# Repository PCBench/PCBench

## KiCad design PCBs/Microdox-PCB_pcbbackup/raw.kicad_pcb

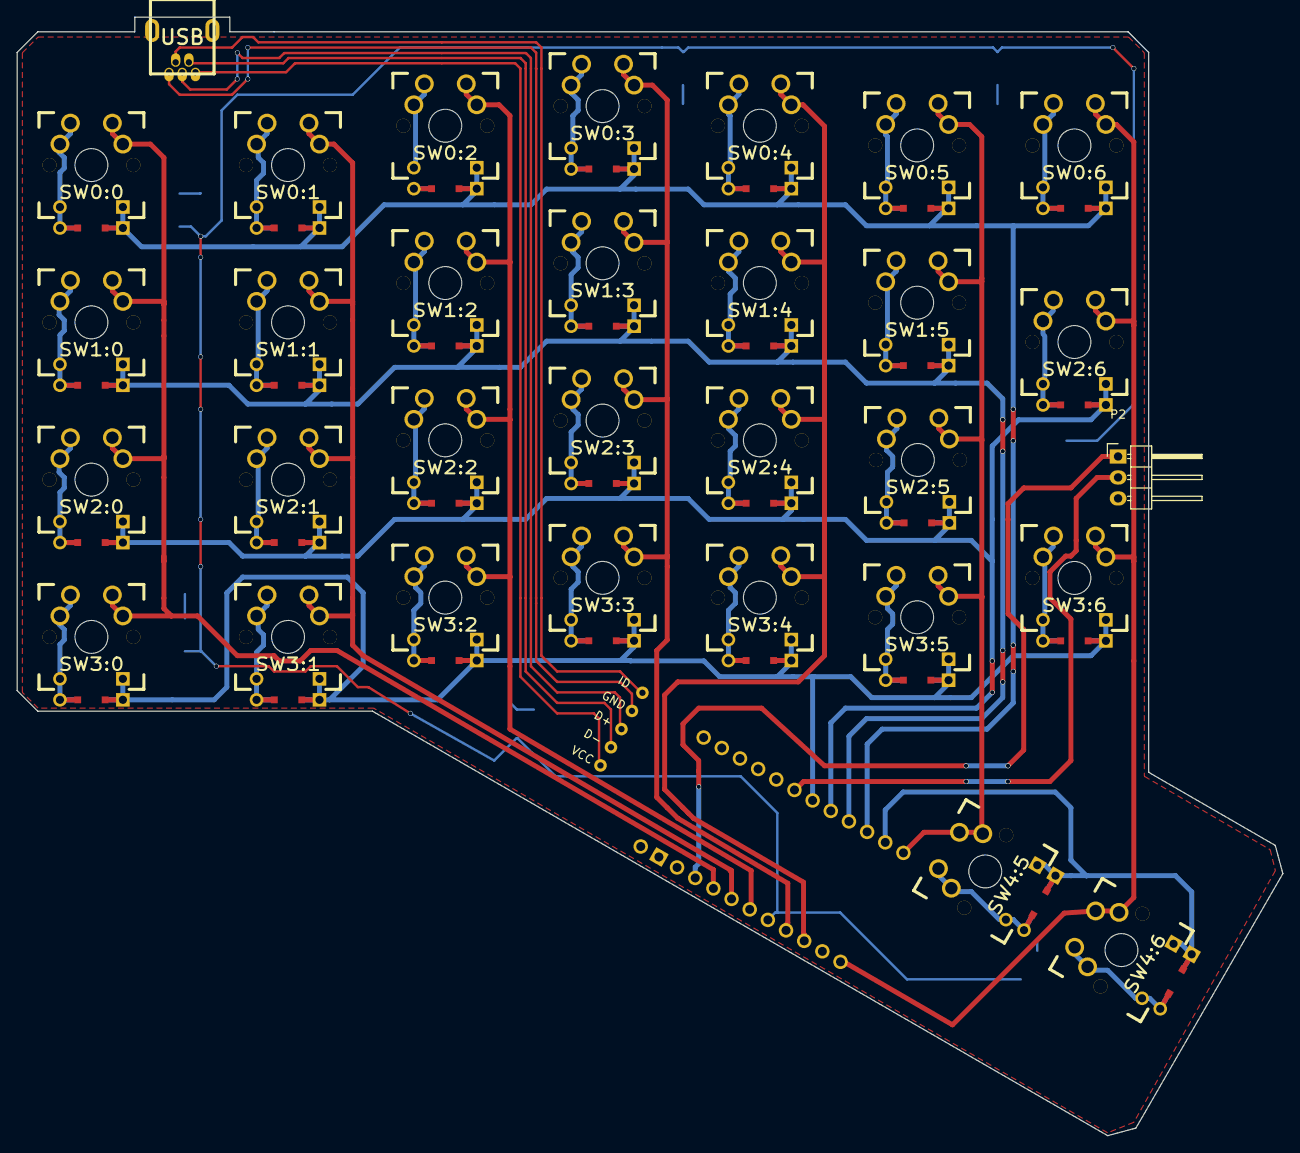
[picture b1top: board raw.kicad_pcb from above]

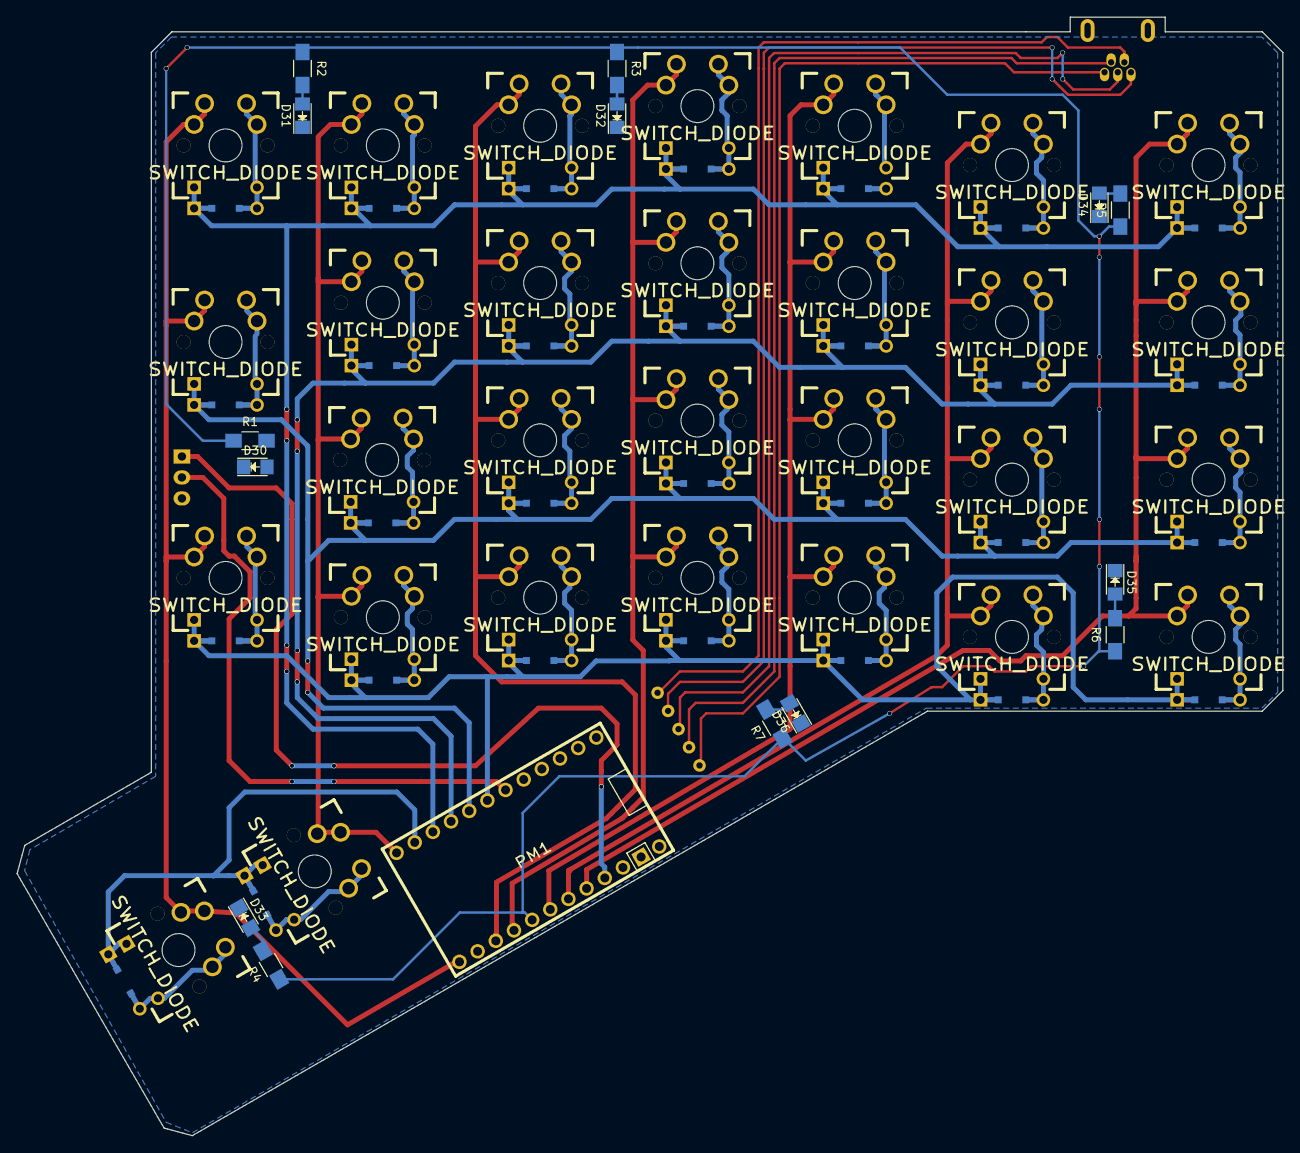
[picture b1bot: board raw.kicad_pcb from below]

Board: 2 copper layers, 153.3 x 135.5 mm, 46 parts (15 on the bottom side), 52 nets.

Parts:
D30, D31, D32, D33, D34, D35, D36: LED; LED_1206
P1: USB; USBMINI
P2: CONN_01X03; Pin_Header_Angled_1x03
PM1: PROMICRO
R1, R2, R3, R4, R5, R6, R7: 100R; R_1206_HandSoldering
SW0:0, SW0:1, SW0:2, SW0:3, SW0:4, SW0:5, SW0:6, SW1:0, SW1:1, SW1:2, SW1:3, SW1:4, SW1:5, SW2:0, SW2:1, SW2:2, SW2:3, SW2:4, SW2:5, SW2:6, SW3:0, SW3:1, SW3:2, SW3:3, SW3:4, SW3:5, SW3:6, SW4:5, SW4:6: SWITCH_DIODE; MX_FLIP_DIODE

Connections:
/COL0: PM1.16, SW0:0.1, SW1:0.1, SW2:0.1, SW3:0.1
/COL1: PM1.17, SW0:1.1, SW1:1.1, SW2:1.1, SW3:1.1
/COL2: PM1.18, SW0:2.1, SW1:2.1, SW2:2.1, SW3:2.1
/COL3: PM1.20, SW0:3.1, SW1:3.1, SW2:3.1, SW3:3.1
/COL4: PM1.21, SW0:4.1, SW1:4.1, SW2:4.1, SW3:4.1
/COL5: PM1.11, SW0:5.1, SW1:5.1, SW2:5.1, SW3:5.1, SW4:5.1
/COL6: PM1.23, SW0:6.1, SW2:6.1, SW3:6.1, SW4:6.1
/LED+: PM1.19, R1.1, R2.1, R3.1, R4.1, R5.1, R6.1, R7.1
/ROW0: PM1.9, SW0:0.4, SW0:1.4, SW0:2.4, SW0:3.4, SW0:4.4, SW0:5.4, SW0:6.4
/ROW1: PM1.8, SW1:0.4, SW1:1.4, SW1:2.4, SW1:3.4, SW1:4.4, SW1:5.4
/ROW2: PM1.7, SW2:0.4, SW2:1.4, SW2:2.4, SW2:3.4, SW2:4.4, SW2:5.4, SW2:6.4
/ROW3: PM1.6, SW3:0.4, SW3:1.4, SW3:2.4, SW3:3.4, SW3:4.4, SW3:5.4, SW3:6.4
/ROW4: PM1.10, SW4:5.4, SW4:6.4
/SER: P2.2, PM1.5
GND: D30.1, D31.1, D32.1, D33.1, D34.1, D35.1, D36.1, P1.6, P2.3, PM1.2, PM1.3, PM1.13
unnamed: D30.2, R1.2
unnamed: D31.2, R2.2
unnamed: D32.2, R3.2
unnamed: D33.2, R4.2
unnamed: D34.2, R5.2
unnamed: D35.2, R6.2
unnamed: D36.2, R7.2
unnamed: SW0:0.2, SW0:0.3
unnamed: SW0:1.2, SW0:1.3
unnamed: SW0:2.2, SW0:2.3
unnamed: SW0:3.2, SW0:3.3
unnamed: SW0:4.2, SW0:4.3
unnamed: SW0:5.2, SW0:5.3
unnamed: SW0:6.2, SW0:6.3
unnamed: SW1:0.2, SW1:0.3
unnamed: SW1:1.2, SW1:1.3
unnamed: SW1:2.2, SW1:2.3
unnamed: SW1:3.2, SW1:3.3
unnamed: SW1:4.2, SW1:4.3
unnamed: SW1:5.2, SW1:5.3
unnamed: SW2:0.2, SW2:0.3
unnamed: SW2:1.2, SW2:1.3
unnamed: SW2:2.2, SW2:2.3
unnamed: SW2:3.2, SW2:3.3
unnamed: SW2:4.2, SW2:4.3
unnamed: SW2:5.2, SW2:5.3
unnamed: SW2:6.2, SW2:6.3
unnamed: SW3:0.2, SW3:0.3
unnamed: SW3:1.2, SW3:1.3
unnamed: SW3:2.2, SW3:2.3
unnamed: SW3:3.2, SW3:3.3
unnamed: SW3:4.2, SW3:4.3
unnamed: SW3:5.2, SW3:5.3
unnamed: SW3:6.2, SW3:6.3
unnamed: SW4:5.2, SW4:5.3
unnamed: SW4:6.2, SW4:6.3
VCC: P2.1, PM1.15

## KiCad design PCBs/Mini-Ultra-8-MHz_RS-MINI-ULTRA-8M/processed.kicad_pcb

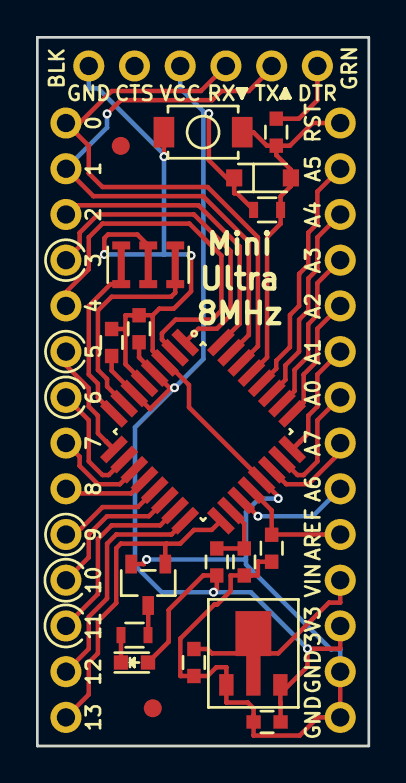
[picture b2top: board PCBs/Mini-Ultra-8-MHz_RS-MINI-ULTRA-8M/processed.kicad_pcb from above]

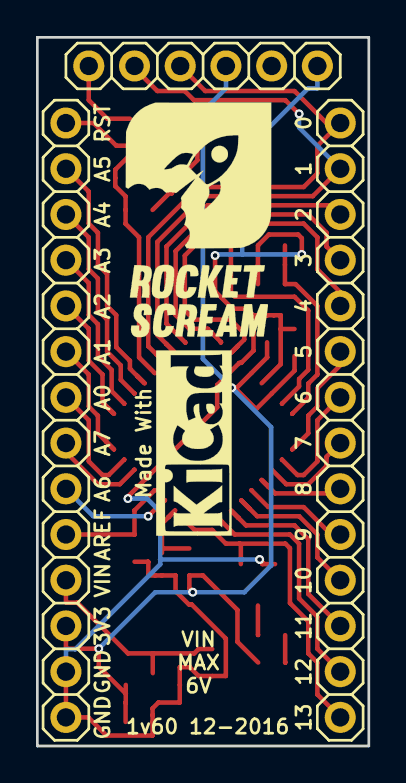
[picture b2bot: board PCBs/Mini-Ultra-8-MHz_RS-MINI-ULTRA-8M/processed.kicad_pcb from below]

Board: 2 copper layers, 18.4 x 39.4 mm, 24 parts (5 on the bottom side), 33 nets.

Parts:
C1, C2, C5, C6, C7: 100nF; C_0603
C3, C4: 1uF 25V X5R; C_0603
D1: 1N4148; SOD-123
D2: Red; LED_0603
J1: 2.54 mm 1x6; HDR_1x6_Pitch2.54mm
J2, J3: 2.54 mm 1x14; HDR_1x14_Pitch2.54mm
L1: LBMF1608T100K; I_0603
LOGO1: LOGO-KICAD; LOGO-KICAD_XSmall
LOGO2: LOGO-ROCKET-SCREAM; LOGO-ROCKET-SCREAM_Vertical_XSmall
M1, M2: FIDUCIAL; FIDUCIAL-1MM
Q1: 2N7002; SOT-23
R1: 10K; R_0603
R2: 1K; R_0603
SW1: SPNO; TS-107A
U1: MCP1700T-3302E/MB; SOT-89
U2: ATMEGA328P-AU; TQFP-32_7x7mm_Pitch0.8mm
Y1: PBRC8.00MR50X000; PBRC-M

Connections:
3V3: C1.1, C2.1, C4.1, D1.1, D2.2, J1.4, J3.12, L1.2, R1.1, U1.3, U2.4, U2.6
/A0: J3.7, U2.23
/A1: J3.6, U2.24
/A2: J3.5, U2.25
/A3: J3.4, U2.26
/A4: J3.3, U2.27
/A5: J3.2, U2.28
/A6: J3.9, U2.19
/A7: J3.8, U2.22
/D0: J1.3, J2.1, U2.30
/D1: J1.2, J2.2, U2.31
/D2: J2.3, U2.32
/D3: J2.4, U2.1
/D4: J2.5, U2.2
/D5: J2.6, U2.9
/D6: J2.7, U2.10
/D7: J2.8, U2.11
/D8: J2.9, U2.12
/D9: J2.10, U2.13
/D10: J2.11, U2.14
/D11: J2.12, U2.15
/D12: J2.13, U2.16
/D13: J2.14, Q1.1, U2.17
/RST: C6.1, D1.2, J3.1, R1.2, SW1.2, U2.29
AREF: C7.1, J3.10, U2.20
GND: C1.2, C2.2, C3.2, C4.2, C5.2, C7.2, J1.6, J3.13, J3.14, Q1.2, SW1.1, U1.1, U2.3, U2.5, U2.21, Y1.2
unnamed: C5.1, L1.1, U2.18
unnamed: C6.2, J1.1
unnamed: D2.1, R2.2
unnamed: Q1.3, R2.1
unnamed: U2.7, Y1.1
unnamed: U2.8, Y1.3
VIN: C3.1, J3.11, U1.2

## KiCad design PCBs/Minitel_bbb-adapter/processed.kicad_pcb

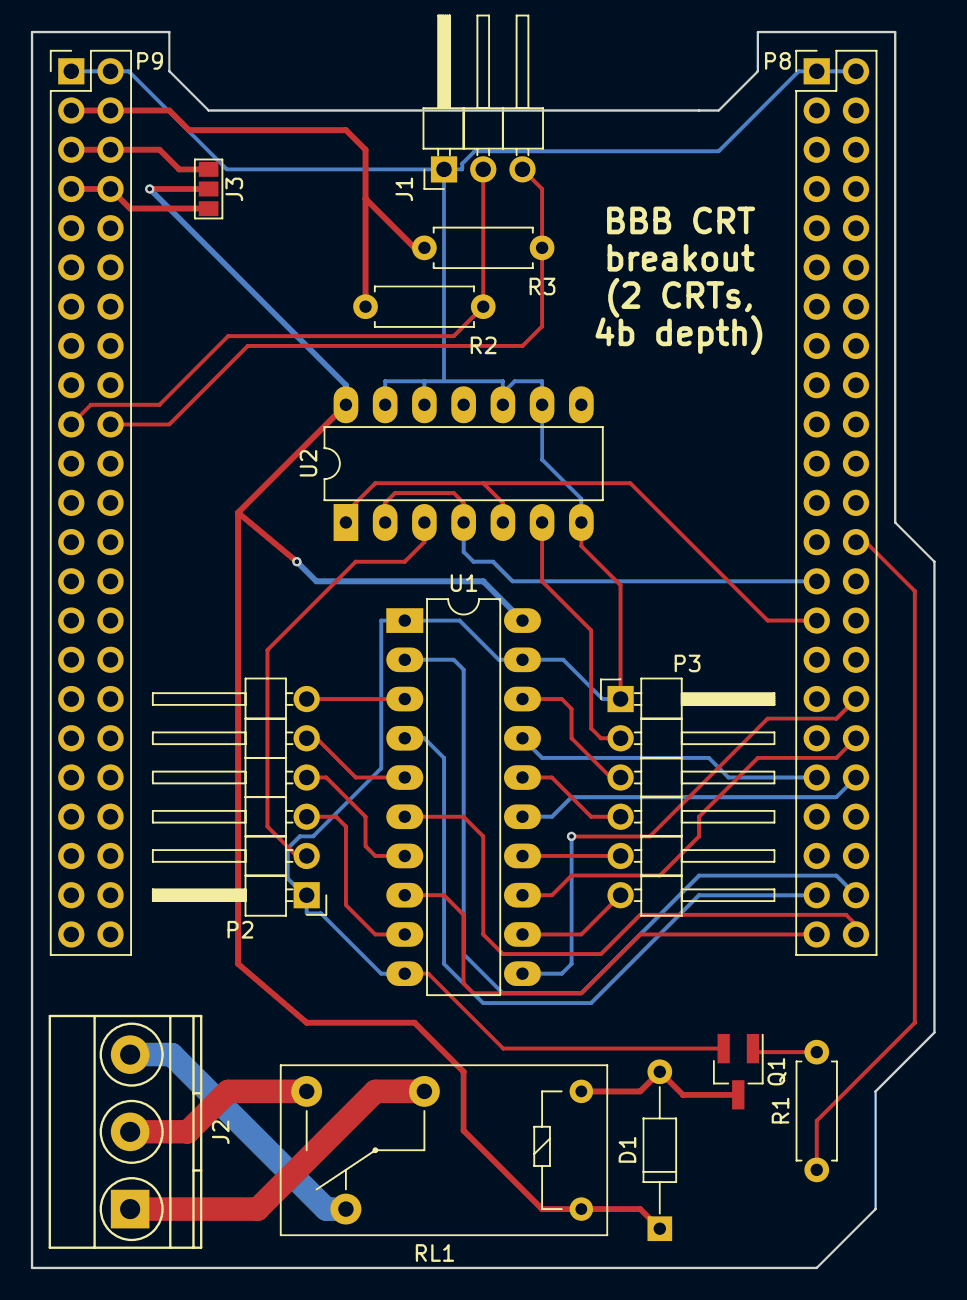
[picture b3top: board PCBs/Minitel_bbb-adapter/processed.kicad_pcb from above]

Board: 2 copper layers, 58.4 x 80.0 mm, 15 parts (0 on the bottom side), 33 nets.

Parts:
D1: 1N4148; D_DO-35_SOD27_P10.16mm_Horizontal
J1: CONN_01X03; Pin_Header_Angled_1x03_Pitch2.54mm
J2: Screw_Terminal_1x03; TerminalBlock_Pheonix_MKDS1.5-3pol
J3: GS3
P2, P3: CONN_01X06; Pin_Header_Angled_1x06_Pitch2.54mm
P8, P9: CONN_02X23; Pin_Header_Straight_2x23_Pitch2.54mm
Q1: Q_NMOS_GSD; SOT-23_Handsoldering
R1: 1K; R_Axial_DIN0207_L6.3mm_D2.5mm_P7.62mm_Horizontal
R2, R3: 4.7K; R_Axial_DIN0207_L6.3mm_D2.5mm_P7.62mm_Horizontal
RL1: G5Q-1; Relay_SPDT_OMRON-G5Q
U1: 74LS244; DIP-20_W7.62mm_LongPads
U2: 74LS32; DIP-14_W7.62mm_LongPads

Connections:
+3V3: P9.3, P9.4, R2.1, R3.1
BB_GPIO1_29: P8.26, R1.1
BB_HSYNC: P8.29, U2.1, U2.5
BB_I2C2_SCL: J1.2, P9.19, R2.2
BB_I2C2_SDA: J1.3, P9.20, R3.2
BB_LCD0: P8.45, U1.8
BB_LCD1: P8.46, U1.6
BB_LCD2: P8.43, U1.4
BB_LCD3: P8.44, U1.2
BB_LCD8: P8.37, U1.17
BB_LCD9: P8.38, U1.15
BB_LCD10: P8.36, U1.13
BB_LCD11: P8.34, U1.11
BB_VSYNC: P8.27, U2.2, U2.4
CSYNC_A: P3.2, U2.6
CSYNC_B: P2.2, U2.3
GND: J1.1, P2.1, P3.1, P8.1, P8.2, P9.1, P9.2, Q1.2, U1.1, U1.10, U1.19, U2.7, U2.9, U2.10, U2.12, U2.13
unnamed: D1.2, Q1.3, RL1.1
unnamed: J2.1, RL1.2
unnamed: J2.2, RL1.3
unnamed: J2.3, RL1.4
unnamed: P2.3, U1.9
unnamed: P2.4, U1.7
unnamed: P2.5, U1.5
unnamed: P2.6, U1.3
unnamed: P3.3, U1.18
unnamed: P3.4, U1.16
unnamed: P3.5, U1.14
unnamed: P3.6, U1.12
unnamed: Q1.1, R1.2
SYS_5V: J3.1, P9.7, P9.8
VCC: D1.1, J3.2, RL1.5, U1.20, U2.14
VDD_5V: J3.3, P9.5, P9.6

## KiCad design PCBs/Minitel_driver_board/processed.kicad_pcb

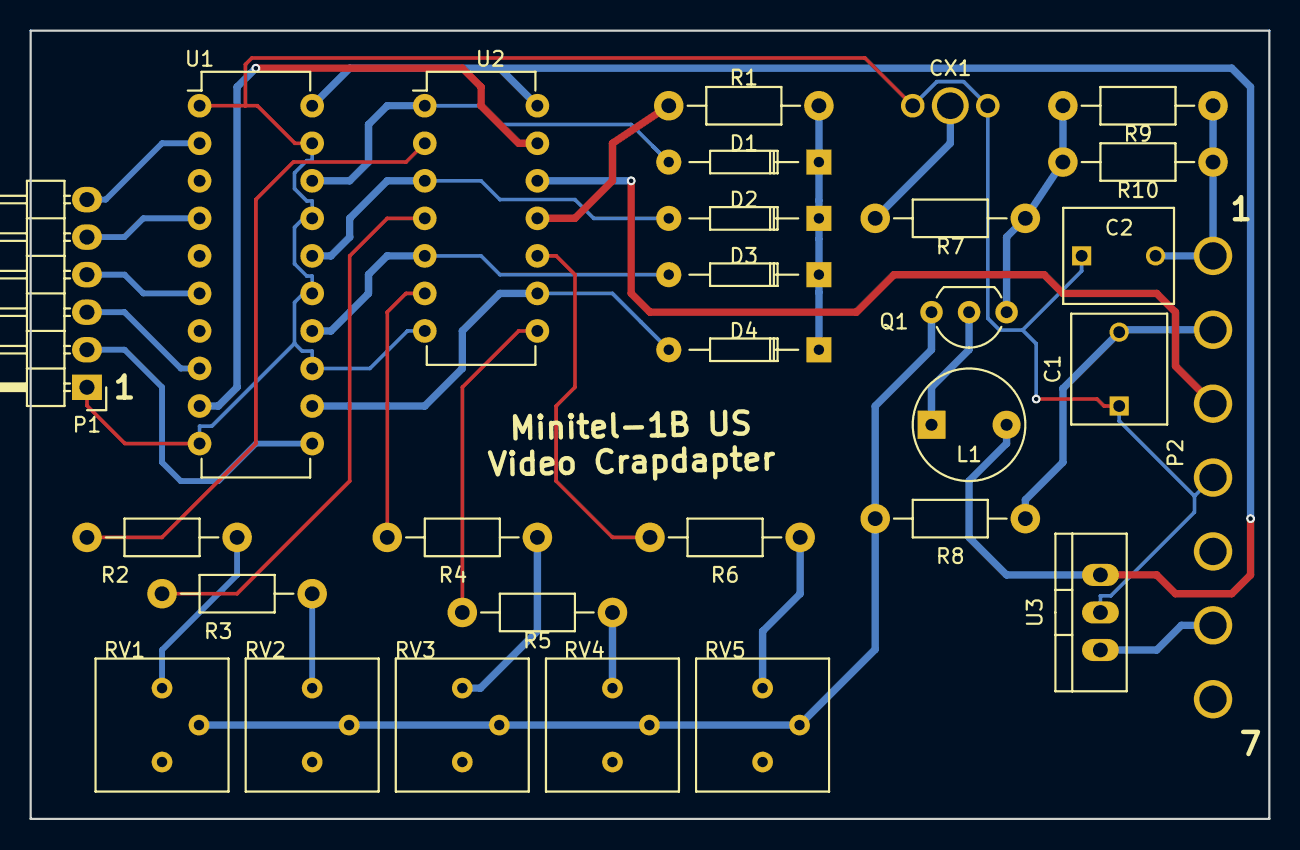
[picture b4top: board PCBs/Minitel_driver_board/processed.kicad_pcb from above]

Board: 2 copper layers, 83.8 x 53.3 mm, 29 parts (0 on the bottom side), 32 nets.

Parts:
C1: 10nF; C_Rect_L7.5_W6.5_P5
C2: 100nF; C_Rect_L7.5_W6.5_P5
CX1: COAX; COAX-SHLD
D1, D2, D3, D4: 1N4148; Diode_DO-35_SOD27_Horizontal_RM10
L1: 20uH; INDUCTOR_V
P1: CONN_01X06; Pin_Header_Angled_1x06
P2: CONN_01X07; CONN-1x7-5mm-pitch
Q1: C5468; TO-92_Inline_Wide
R1: 680; Resistor_Horizontal_RM10mm
R2: 4K; Resistor_Horizontal_RM10mm
R3: 1.8K; Resistor_Horizontal_RM10mm
R4: 1K; Resistor_Horizontal_RM10mm
R5: 460; Resistor_Horizontal_RM10mm
R6: 620; Resistor_Horizontal_RM10mm
R7: 100; Resistor_Horizontal_RM10mm
R8: 1.2K; Resistor_Horizontal_RM10mm
R9, R10: 2.4K; Resistor_Horizontal_RM10mm
RV1, RV2, RV3, RV4, RV5: POT; Potentiometer_Cermet_CT-6EP
U1: 74LS244; DIP-20_W7.62mm
U2: 74HC04; DIP-14_W7.62mm
U3: 7805; TO-220_Neutral123_Vertical

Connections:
GND: C1.1, C2.1, CX1.2, CX1.3, P1.1, P2.4, U1.1, U1.10, U1.13, U1.15, U1.17, U1.19, U2.7, U3.2
unnamed: C1.2, P2.2, R8.1
unnamed: C2.2, P2.1, R9.1, R10.1
unnamed: CX1.1, R7.1
unnamed: D1.1, D2.1, D3.1, D4.1, R1.2
unnamed: D1.2, U1.18, U2.1
unnamed: D2.2, U1.16, U2.3
unnamed: D3.2, U1.14, U2.5
unnamed: D4.2, U1.12, U2.9
unnamed: L1.1, Q1.2
unnamed: P1.2, U1.11
unnamed: P1.3, U1.8
unnamed: P1.4, U1.6
unnamed: P1.5, U1.4
unnamed: P1.6, U1.2
unnamed: P2.3, U2.12
unnamed: P2.6, U3.1
unnamed: Q1.1, R7.2, R9.2, R10.2
unnamed: Q1.3, R8.2, RV1.2, RV2.2, RV3.2, RV4.2, RV5.2
unnamed: R1.1, U2.11
unnamed: R2.1, RV1.1
unnamed: R2.2, U2.2
unnamed: R3.1, RV2.1
unnamed: R3.2, U2.4
unnamed: R4.1, RV3.1
unnamed: R4.2, U2.6
unnamed: R5.1, RV4.1
unnamed: R5.2, U2.8
unnamed: R6.1, RV5.1
unnamed: R6.2, U2.10
SYNC: U1.9, U2.13
VCC: L1.2, U1.20, U2.14, U3.3

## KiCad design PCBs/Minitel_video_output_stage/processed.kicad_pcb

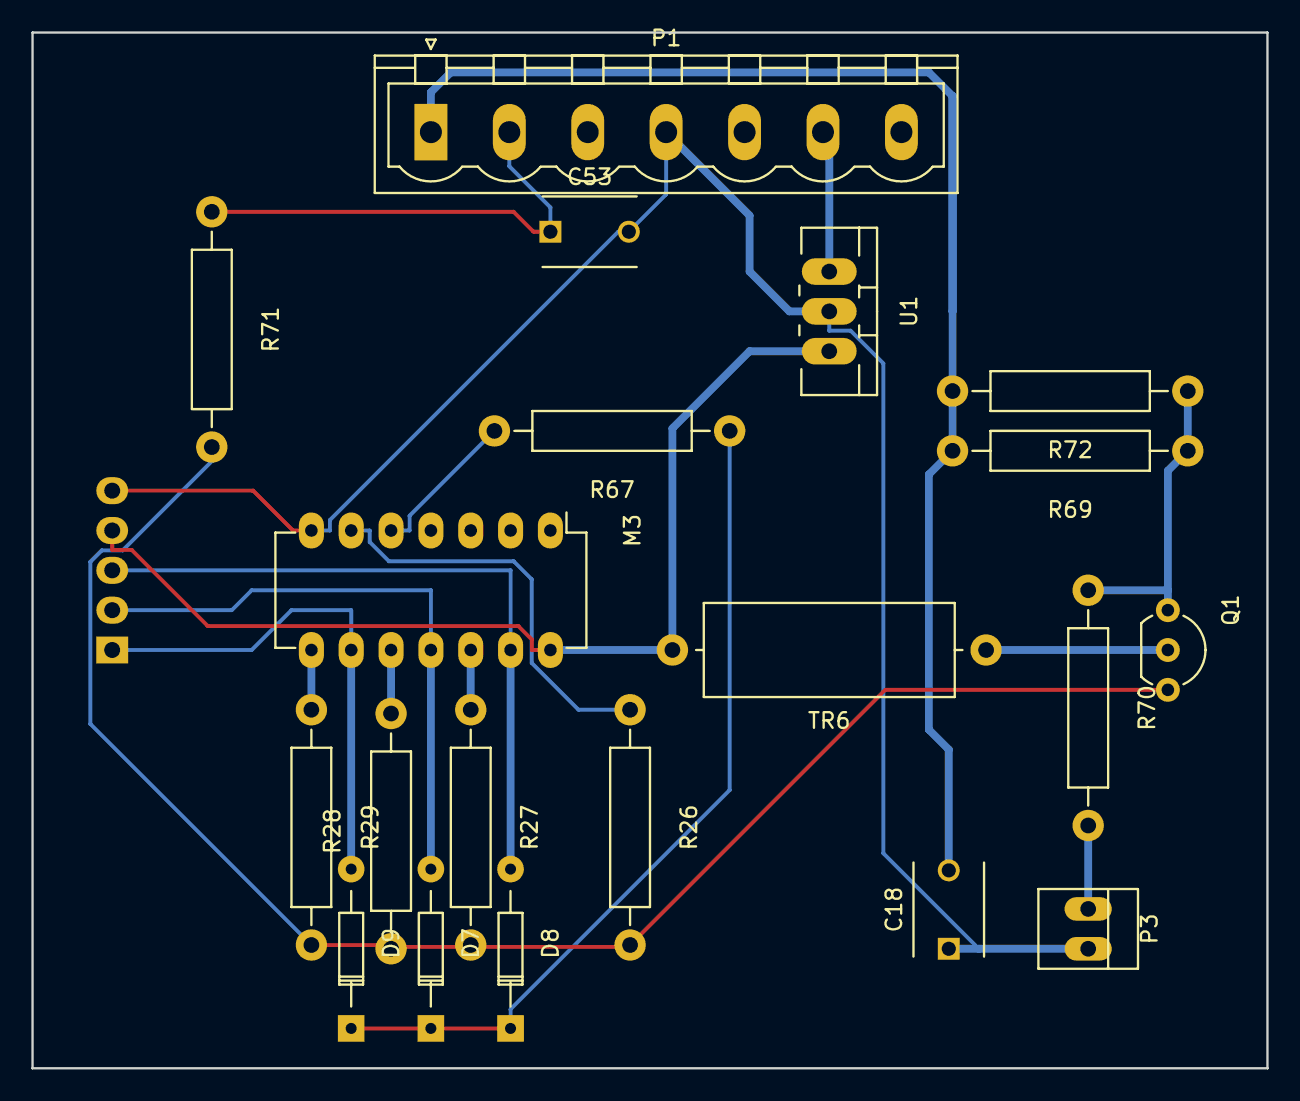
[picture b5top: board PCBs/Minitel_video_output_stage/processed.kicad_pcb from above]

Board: 2 copper layers, 78.7 x 66.0 mm, 21 parts (1 on the bottom side), 18 nets.

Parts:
C18: 100nF; C_Disc_D6_P5
C53: 10nF; C_Disc_D6_P5
D7, D8, D9: 1N4148; Diode_DO-35_SOD27_Horizontal_RM10
M3: 74HC04; DIP-14_W7.62mm_LongPads
P1: CONN_01X07; PhoenixContact_MSTBVA-G_07x5.00mm_Vertical
P2: CONN_01X05; Pin_Header_Straight_1x05
P3: BNC; PINHEAD1-2
Q1: C5468; TO-92_Inline_Wide
R26: 620; Resistor_Horizontal_RM15mm
R27: 1.8K; Resistor_Horizontal_RM15mm
R28: 460; Resistor_Horizontal_RM15mm
R29: 1K; Resistor_Horizontal_RM15mm
R67: 670; Resistor_Horizontal_RM15mm
R69, R72: 2.4K; Resistor_Horizontal_RM15mm
R70: 100; Resistor_Horizontal_RM15mm
R71: 1.2K; Resistor_Horizontal_RM15mm
TR6: 20uH; Choke_Horizontal_RM20mm
U1: 7805; TO-220_Neutral123_Vertical_LargePads

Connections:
+5V: M3.14, P2.4, TR6.2, U1.3
CH_BLUE: D9.2, M3.9, P2.1
CH_GREEN: D7.2, M3.11, P2.2
CH_RED: D8.2, M3.13, P2.3
GND: C18.1, C53.2, M3.7, P1.4, P2.5, P3.2, U1.2
unnamed: C18.2, P1.1, R69.2, R72.2
unnamed: C53.1, P1.2, R71.1
unnamed: D7.1, D8.1, D9.1, R67.1
unnamed: M3.5, R67.2
unnamed: M3.6, R26.1
unnamed: M3.8, R29.1
unnamed: M3.10, R28.2
unnamed: M3.12, R27.1
unnamed: Q1.1, R69.1, R70.1, R72.1
unnamed: Q1.2, TR6.1
unnamed: Q1.3, R26.2, R27.2, R28.1, R29.2, R71.2
VIDEO_OUT: P3.1, R70.2
VIN: P1.6, U1.1

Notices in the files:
PCBs/MoonLander_MoonLander/processed.kicad_pcb:
CC BY-SA
